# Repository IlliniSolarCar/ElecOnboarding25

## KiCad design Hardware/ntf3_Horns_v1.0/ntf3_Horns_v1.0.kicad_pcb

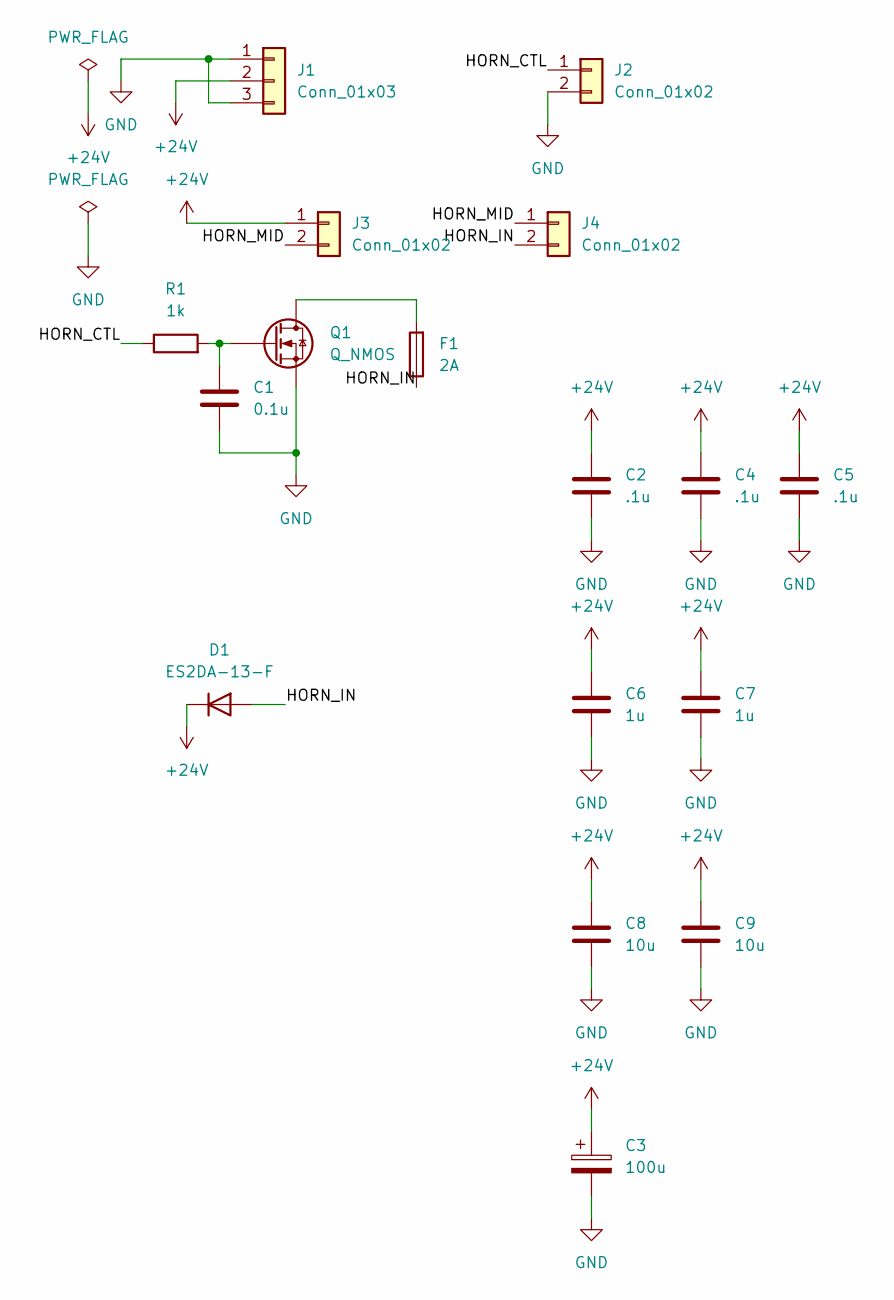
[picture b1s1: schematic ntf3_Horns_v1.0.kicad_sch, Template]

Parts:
C1: 0.1u; C_0805_2012Metric
C2, C4, C5: .1u; C_0805_2012Metric
C3: 100u; CP_Radial_D8.0mm_P3.50mm
C6, C7: 1u; C_0805_2012Metric
C8, C9: 10u; C_0805_2012Metric
D1: ES2DA-13-F; D_SMA
F1: 2A; Fuse_1206_3216Metric
J1: Conn_01x03; JST_XH_B3B-XH-A_1x03_P2.50mm_Vertical
J2, J3, J4: Conn_01x02; JST_XH_B2B-XH-A_1x02_P2.50mm_Vertical
Q1: Q_NMOS; TO-252-3_TabPin2
R1: 1k; R_0805_2012Metric

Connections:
+24V: C2.1, C3.1, C4.1, C5.1, C6.1, C7.1, C8.1, C9.1, D1.1 (K), J1.2, J3.1
/HORN_CTL: J2.1, R1.1
/HORN_IN: D1.2 (A), F1.1, J4.2
/HORN_MID: J3.2, J4.1
GND: C1.2, C2.2, C3.2, C4.2, C5.2, C6.2, C7.2, C8.2, C9.2, J1.1, J1.3, J2.2, Q1.3 (S)
unnamed: F1.2, Q1.2 (D)
unnamed: C1.1, Q1.1 (G), R1.2

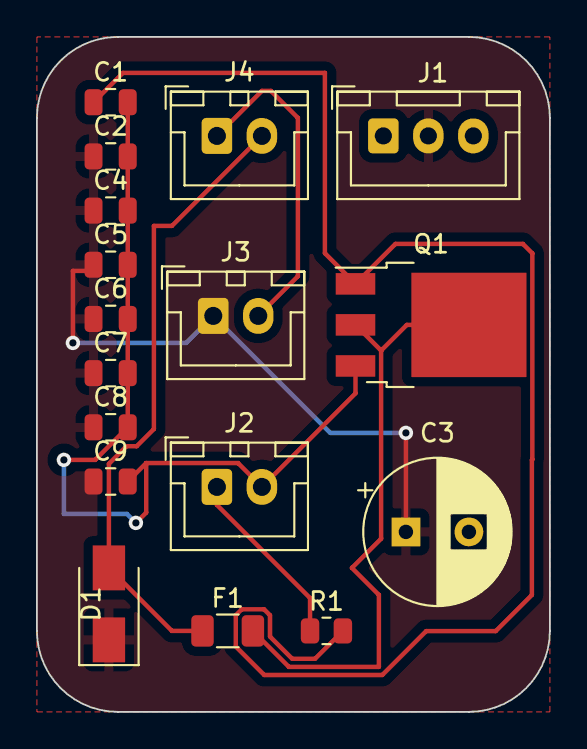
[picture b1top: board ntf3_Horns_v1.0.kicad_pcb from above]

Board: 2 copper layers, 28.5 x 37.5 mm, 17 parts (0 on the bottom side), 7 nets.

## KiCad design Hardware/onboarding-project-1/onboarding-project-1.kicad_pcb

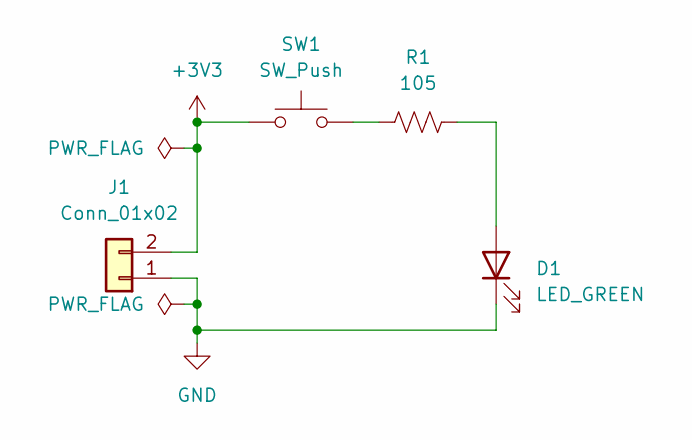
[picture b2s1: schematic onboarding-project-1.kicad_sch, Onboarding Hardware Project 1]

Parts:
D1: LED_GREEN; LED_0603_Symbol_on_F.SilkS
J1: Conn_01x02; Molex_KK-254_AE-6410-02A_1x02_P2.54mm_Vertical; MPN 022272021
R1: 105; R_0603_1608Metric_Pad0.98x0.95mm_HandSolder
SW1: SW_Push; SW_DIP_SPSTx01_Slide_6.7x4.1mm_W8.61mm_P2.54mm_LowProfile; MPN 1825910-6

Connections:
+3V3: J1.2, SW1.1
GND: D1.1 (K), J1.1
unnamed: D1.2 (A), R1.2
unnamed: R1.1, SW1.2

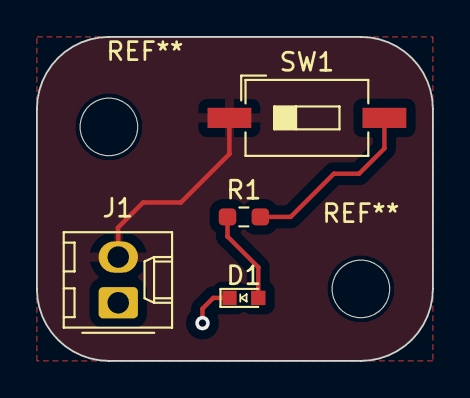
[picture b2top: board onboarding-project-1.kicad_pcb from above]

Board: 2 copper layers, 22.0 x 18.0 mm, 4 parts (0 on the bottom side), 4 nets.

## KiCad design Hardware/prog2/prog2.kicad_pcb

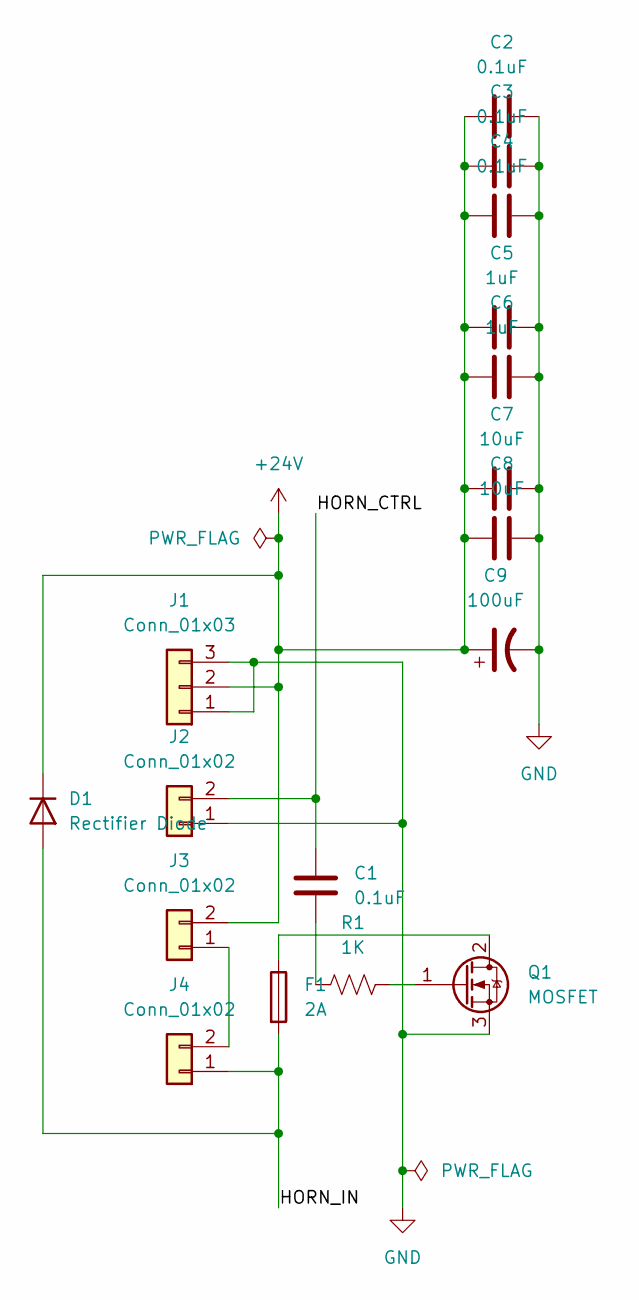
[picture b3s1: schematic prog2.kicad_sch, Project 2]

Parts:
C1, C2, C3, C4: 0.1uF; C_0201_0603Metric_Pad0.64x0.40mm_HandSolder
C5, C6: 1uF; C_0402_1005Metric_Pad0.74x0.62mm_HandSolder
C7, C8: 10uF; C_0504_1310Metric_Pad0.83x1.28mm_HandSolder
C9: 100uF; C_0805_2012Metric_Pad1.18x1.45mm_HandSolder
D1: Rectifier Diode; D_SMA; MPN US2DA
F1: 2A; Fuse_0603_1608Metric_Pad1.05x0.95mm_HandSolder
J1: Conn_01x03; Molex_Micro-Fit_3.0_43650-0300_1x03_P3.00mm_Horizontal; MPN 436500300
J2, J3, J4: Conn_01x02; Molex_Micro-Fit_3.0_43650-0210_1x02-1MP_P3.00mm_Horizontal; MPN 022272021
Q1: MOSFET; TO-252-2; MPN STD7NK40Z
R1: 1K; R_0603_1608Metric_Pad0.98x0.95mm_HandSolder

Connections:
+24V: C2.1, C3.2, C4.1, C5.1, C6.1, C7.1, C8.1, C9.1, D1.1 (K), J1.2, J3.2
/HORN_CTRL: C1.1, J2.2
/HORN_IN: D1.2 (A), F1.2, J4.1
GND: C2.2, C3.1, C4.2, C5.2, C6.2, C7.2, C8.2, C9.2, J1.1, J1.3, J2.1, Q1.3 (S)
unnamed: C1.2, R1.1
unnamed: J3.1, J4.2
unnamed: F1.1, Q1.2 (D)
unnamed: Q1.1 (G), R1.2

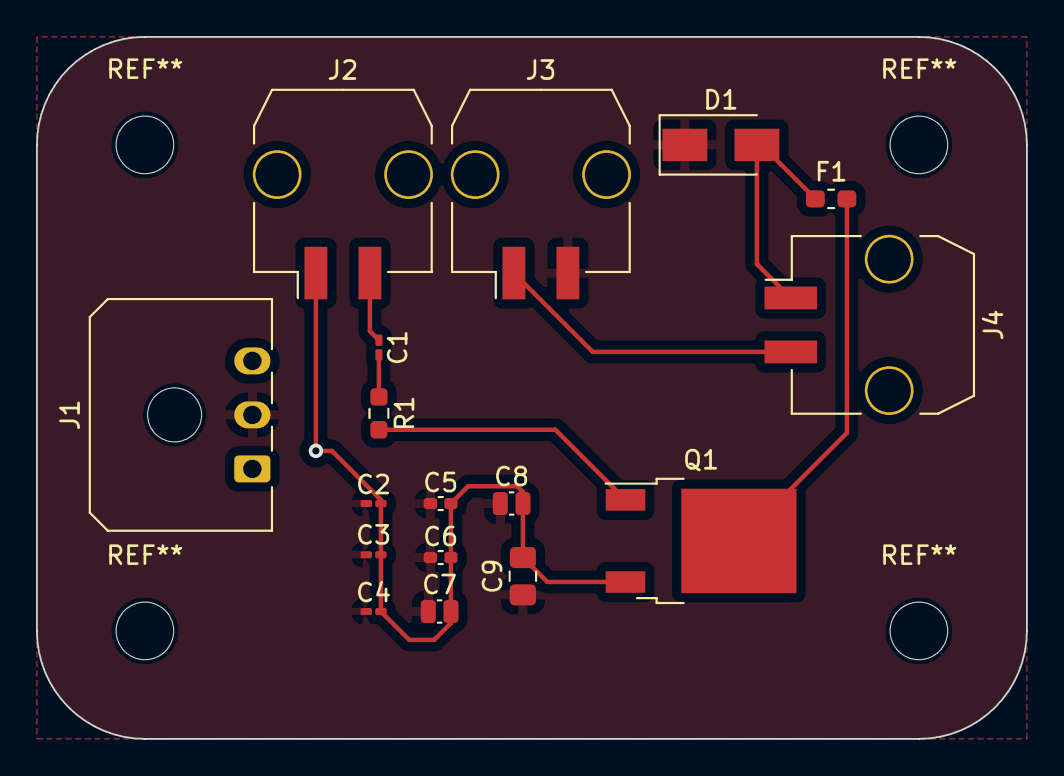
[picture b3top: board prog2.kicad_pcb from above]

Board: 2 copper layers, 55.0 x 39.0 mm, 17 parts (0 on the bottom side), 8 nets.
